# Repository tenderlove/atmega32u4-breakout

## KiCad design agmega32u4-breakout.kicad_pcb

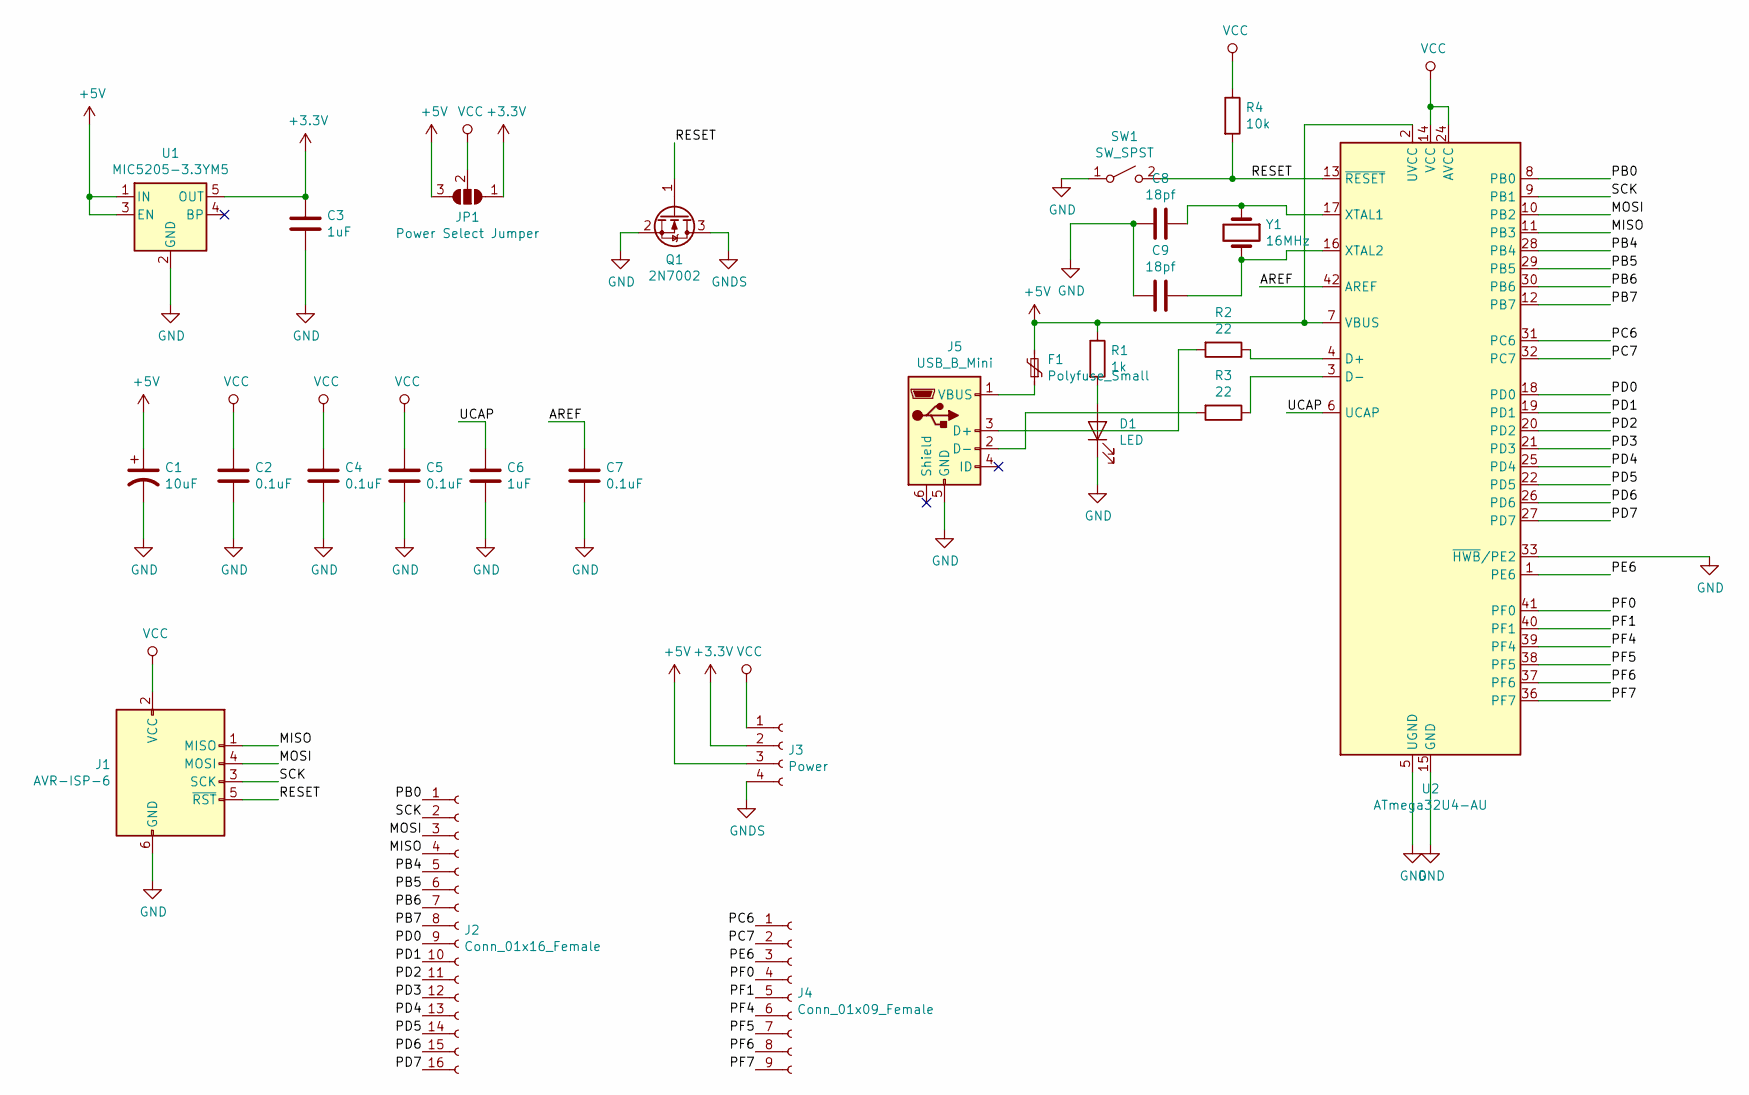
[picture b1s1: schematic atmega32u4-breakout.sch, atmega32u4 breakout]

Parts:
C1: 10uF; C_1206_3216Metric; LCSC C7171
C2, C4, C5, C7: 0.1uF; C_0603_1608Metric; LCSC C14663
C3, C6: 1uF; C_0603_1608Metric; LCSC C15849
C8, C9: 18pf; C_0603_1608Metric; LCSC C1647
D1: LED; LED_0603_1608Metric; LCSC C2286
F1: Polyfuse_Small; Fuse_2920_7451Metric; LCSC C207089
J1: AVR-ISP-6; IDC-Header_2x03_P2.54mm_Vertical
J2: Conn_01x16_Female; PinHeader_1x16_P2.54mm_Vertical
J3: Power; PinHeader_1x04_P2.54mm_Vertical
J4: Conn_01x09_Female; PinHeader_1x09_P2.54mm_Vertical
J5: USB_B_Mini; USB_Mini-B_Lumberg_2486_01_Horizontal
JP1: Power Select Jumper; SolderJumper-3_P1.3mm_Open_Pad1.0x1.5mm
Q1: 2N7002; SOT-23; LCSC C8545
R1: 1k; R_0603_1608Metric; LCSC C21190
R2, R3: 22; R_0603_1608Metric; LCSC C23345
R4: 10k; R_0603_1608Metric; LCSC C25804
SW1: SW_SPST; SW_Cherry_MX_1.00u_PCB
U1: MIC5205-3.3YM5; SOT-23-5; LCSC C37970
U2: ATmega32U4-AU; TQFP-44_10x10mm_P0.8mm; LCSC C44854
Y1: 16MHz; Crystal_SMD_3225-4Pin_3.2x2.5mm; LCSC C13738

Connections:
+3V3: C3.1, J3.2, JP1.1 (A), U1.5 (OUT)
+5V: C1.1, F1.2, J3.3, JP1.3 (B), R1.1, U1.1 (IN), U1.3 (EN), U2.2 (UVCC), U2.7 (VBUS)
/AREF: C7.1, U2.42 (AREF)
/MISO: J1.1 (MISO), J2.4, U2.11 (PB3)
/MOSI: J1.4 (MOSI), J2.3, U2.10 (PB2)
/PB0: J2.1, U2.8 (PB0)
/PB4: J2.5, U2.28 (PB4)
/PB5: J2.6, U2.29 (PB5)
/PB6: J2.7, U2.30 (PB6)
/PB7: J2.8, U2.12 (PB7)
/PC6: J4.1, U2.31 (PC6)
/PC7: J4.2, U2.32 (PC7)
/PD0: J2.9, U2.18 (PD0)
/PD1: J2.10, U2.19 (PD1)
/PD2: J2.11, U2.20 (PD2)
/PD3: J2.12, U2.21 (PD3)
/PD4: J2.13, U2.25 (PD4)
/PD5: J2.14, U2.22 (PD5)
/PD6: J2.15, U2.26 (PD6)
/PD7: J2.16, U2.27 (PD7)
/PE6: J4.3, U2.1 (PE6)
/PF0: J4.4, U2.41 (PF0)
/PF1: J4.5, U2.40 (PF1)
/PF4: J4.6, U2.39 (PF4)
/PF5: J4.7, U2.38 (PF5)
/PF6: J4.8, U2.37 (PF6)
/PF7: J4.9, U2.36 (PF7)
/RESET: J1.5 (~RST), Q1.1 (G), R4.2, SW1.2 (B), U2.13 (~RESET)
/SCK: J1.3 (SCK), J2.2, U2.9 (PB1)
/UCAP: C6.1, U2.6 (UCAP)
GND: C1.2, C2.2, C3.2, C4.2, C5.2, C6.2, C7.2, C8.2, C9.2, D1.1 (K), J1.6 (GND), J5.5 (GND), Q1.2 (S), SW1.1 (A), U1.2 (GND), U2.5 (UGND), U2.15 (GND), U2.23 (GND), U2.33 (~HWB~/PE2), U2.35 (GND), U2.43 (GND)
GNDS: J3.4, Q1.3 (D)
unnamed: C8.1, U2.17 (XTAL1), Y1.1
unnamed: C9.1, U2.16 (XTAL2), Y1.2
unnamed: D1.2 (A), R1.2
unnamed: F1.1, J5.1 (VBUS)
unnamed: J5.2 (D-), R3.2
unnamed: J5.3 (D+), R2.2
unnamed: R2.1, U2.4 (D+)
unnamed: R3.1, U2.3 (D-)
VCC: C2.1, C4.1, C5.1, J1.2 (VCC), J3.1, JP1.2 (C), R4.1, U2.14 (VCC), U2.24 (AVCC), U2.34 (VCC), U2.44 (AVCC)

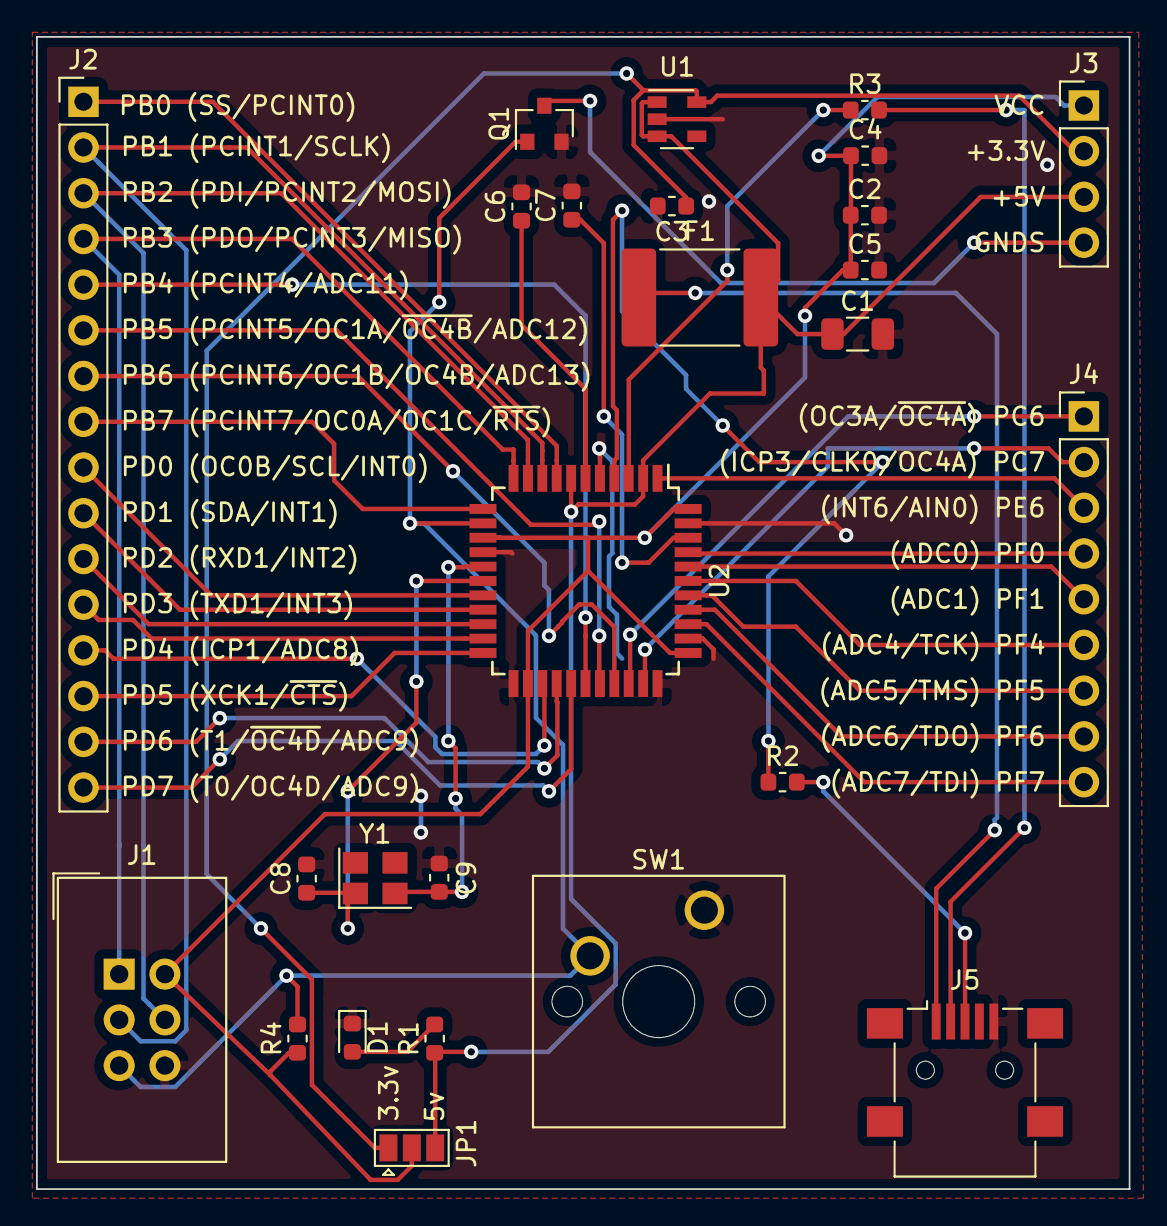
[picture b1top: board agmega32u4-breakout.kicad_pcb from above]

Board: 2 copper layers, 60.7 x 64.0 mm, 26 parts (0 on the bottom side), 41 nets.

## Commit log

2020-05-14 initial
2020-05-14 fixing name
